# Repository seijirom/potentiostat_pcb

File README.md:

# potentiostat_pcb
- 1st PCB design(branch: master): routing 1st cut (commit:2fe1972c45b8e02d9013573033267965fc6c9423)
- 2nd PCB design(branch: 2nd_make): Modified by kou (commit:4e592e7a58986544d3452f250c1e05fc51d4db7a)
- 3rd PCB design: work in progress in 3rd_make branch

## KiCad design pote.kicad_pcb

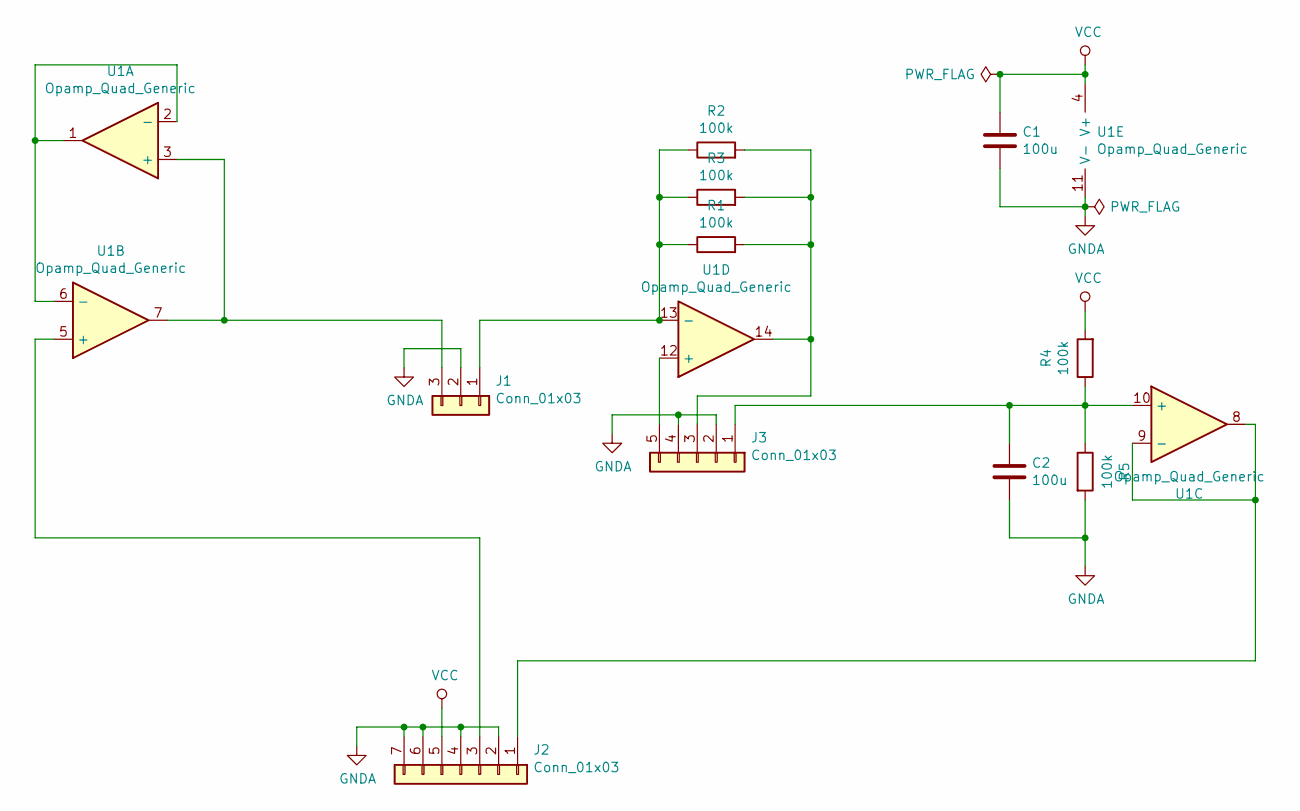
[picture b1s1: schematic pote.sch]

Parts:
C1, C2: 100u; CP_Radial_D8.0mm_P3.50mm
J1: Conn_01x03; PinHeader_1x03_P2.54mm_Vertical
J2: Conn_01x03; PinHeader_1x07_P2.54mm_Vertical
J3: Conn_01x03; PinHeader_1x05_P2.54mm_Vertical
R1, R2, R3, R4, R5: 100k; R_Axial_DIN0207_L6.3mm_D2.5mm_P10.16mm_Horizontal
U1: Opamp_Quad_Generic; SSOP-14_5.3x6.2mm_Pitch0.65mm

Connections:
GNDA: C1.2, C2.2, J1.2, J2.2, J2.4, J2.6, J2.7, J3.2, J3.4, R5.2, U1.11 (V-)
unnamed: C2.1, J3.1, R4.1, R5.1, U1.10 (+)
unnamed: J1.1, R1.1, R2.1, R3.1, U1.13 (-)
unnamed: J1.3, U1.3 (+), U1.7
unnamed: J2.1, U1.8, U1.9 (-)
unnamed: J2.3, U1.5 (+)
unnamed: J3.3, R1.2, R2.2, R3.2, U1.14
unnamed: J3.5, U1.12 (+)
unnamed: U1.1, U1.2 (-), U1.6 (-)
VCC: C1.1, J2.5, R4.2, U1.4 (V+)

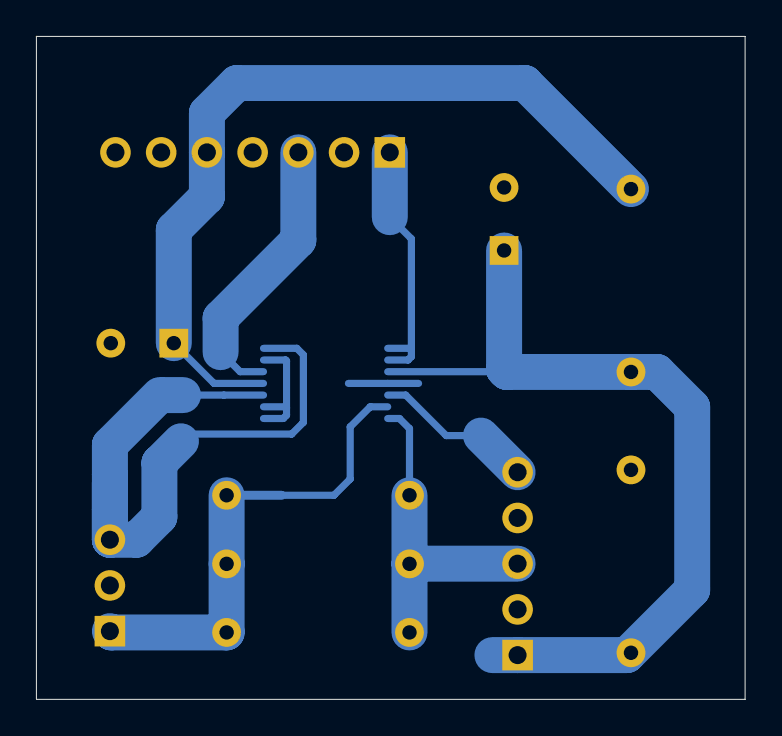
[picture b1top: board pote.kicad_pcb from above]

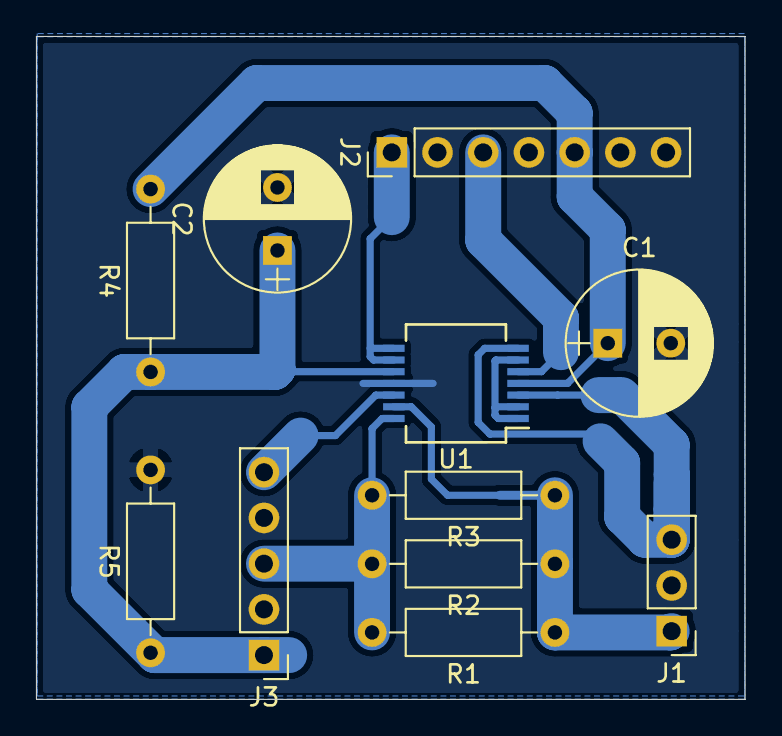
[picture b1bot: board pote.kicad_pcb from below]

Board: 2 copper layers, 39.4 x 36.8 mm, 11 parts (11 on the bottom side), 10 nets.

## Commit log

2019-12-20 placement 1st cut and routing WIP
2019-12-20 routing 1st cut
2019-12-21 Modified by kou
